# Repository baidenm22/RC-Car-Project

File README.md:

# RC Car Project
This is the repository for all the files in our RC Car Project at BYU in Fall 2026

## The Idea
The goal of this project is to build an RC Car and controller using a microcontroller. We have the following learning goals:
  - Make a PCB
  - Apply our learning of circuits
  - Practice documentation
  - practice using git
  - Create a controller that can be used in all future projects
  - Create friendship
  - Will Simmons needs to lock in
  - Will are you even seeing this
  - Will we need you to do the math

## What is needed

| Car Componets | Controller Components |
|:----------:|:-------------:|
| Arduino Nano | Arduino ESP32 Nano |
| nRF24l01 | nRf24l01 |
| 2 3-6v Motor | L2C OLED |
| Angle Servo | Joystick |
| H-Bridge (L293D) | 4 Buttons

### How we are currently connecting our project to the microcontroller

#### Controller
| Pin | Componet | 
|:----:|:----:|
|VIN|5v Regulator|
|GND	|GND|
|3.3V|nRF24l01 VCC|
|D13	|nRF24l01 SCK|
|D12	|nRF24l01 MISO|
|D11|	nRF24l01 MOSI|
|D10|	Button 1|
|D9|	Button 2|
|D8|	nRF24l01 CSN|
|D7|	nRF24l01 CE|
|D6| Joystick button SW|
|D3|	Button 3|
|D2|	Button 4|
|A1|	Joystick VRY|
|A2|	Joystick VRX|
|A4| L2C OLED SDA|
|A5| L2C OLED SCL|

#### Car
| Pin | Componet | 
|:----:|:----:|
|VIN|	5v Regulator|
|GND|	GND|
|3.3V|	nRF24l01 VCC|
|D13|	nRF24l01 SCK|
|D12|	nRF24l01 MISO|
|D11|	nRF24l01 MOSI|
|D10|	Right Motor INPUT 1|
|D9|	Right Motor INPUT 2|
|D8|	nRF24l01 CSN|
|D7|	nRF24l01 CE|
|D6|	Servo Instructions|
|D5|	Right Motor PWM Speed|
|D4|	IR Sensor INPUT|
|D3|	Left Motor PWM Speed|
|D2|	Left Motor INPUT 3|
|D1|	Left Motor INPUT 4|

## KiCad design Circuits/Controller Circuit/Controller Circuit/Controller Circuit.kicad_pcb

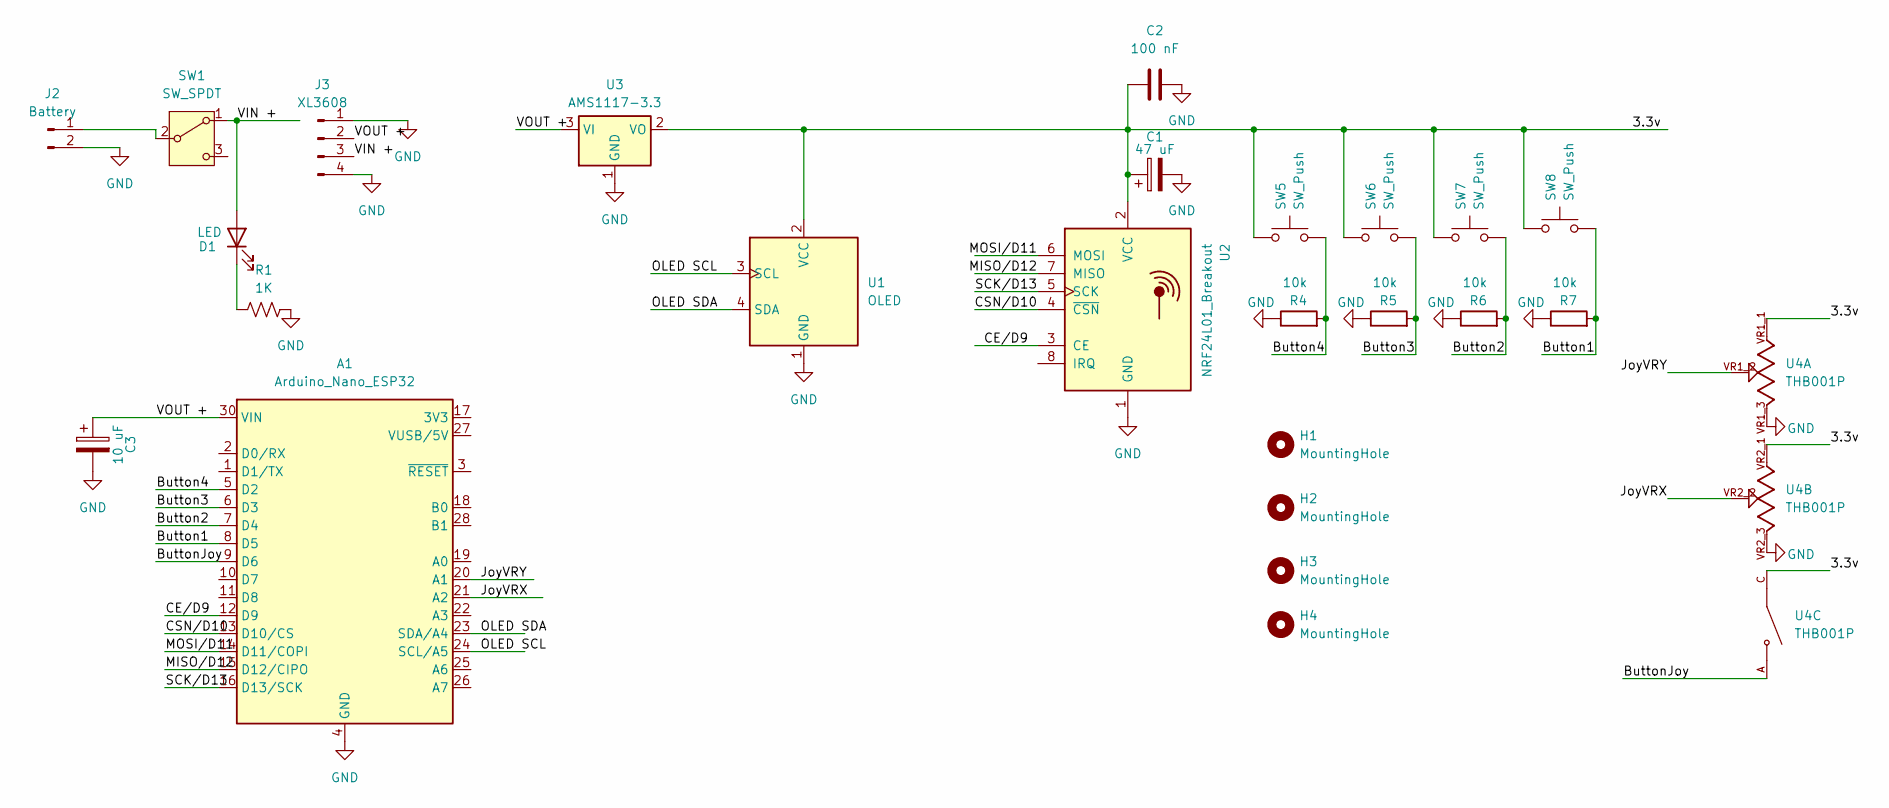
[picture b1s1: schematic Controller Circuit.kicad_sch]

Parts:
A1: Arduino_Nano_ESP32; Arduino_Nano
C1: 47 uF; CP_Radial_D8.0mm_P3.50mm
C2: 100 nF; C_Disc_D4.7mm_W2.5mm_P5.00mm
C3: 10 uF; CP_Radial_D5.0mm_P2.50mm
D1: LED; LED_Oval_W5.2mm_H3.8mm
H1, H2, H3, H4: MountingHole; MountingHole_3.2mm_M3
J2: Battery; SolderWire-0.1sqmm_1x02_P3.6mm_D0.4mm_OD1mm
J3: XL3608; 5V Booster
R1: 1K; R_Axial_DIN0204_L3.6mm_D1.6mm_P5.08mm_Horizontal
R4, R5, R6, R7: 10k; R_Axial_DIN0204_L3.6mm_D1.6mm_P5.08mm_Horizontal
SW1: SW_SPDT; SW_Slide_10mm
SW5, SW6, SW7, SW8: SW_Push; SW_PUSH_6mm
U1: OLED; ER_OLEDM0.91_1x-I2C
U2: NRF24L01_Breakout; nRF24L01_Breakout
U3: AMS1117-3.3; PinSocket_1x03_P2.54mm_Horizontal
U4: THB001P; CNK_THB001P; MPN THB001P

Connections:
/3.3v: C1.1, C2.2, SW5.1, SW6.1, SW7.1, SW8.1, U1.2 (VCC), U2.2 (VCC), U3.2 (VO), U4.C, U4.D, U4.VR1_1, U4.VR2_1
/Button1: A1.8 (D5), R7.2, SW8.2
/Button2: A1.7 (D4), R6.2, SW7.2
/Button3: A1.6 (D3), R5.2, SW6.2
/Button4: A1.5 (D2), R4.2, SW5.2
/ButtonJoy: A1.9 (D6), U4.A, U4.B
/CE/D9: A1.12 (D9), U2.3 (CE)
/CSN/D10: A1.13 (D10/CS), U2.4 (~CSN)
/JoyVRX: A1.21 (A2), U4.VR2_2
/JoyVRY: A1.20 (A1), U4.VR1_2
/MISO/D12: A1.15 (D12/CIPO), U2.7 (MISO)
/MOSI/D11: A1.14 (D11/COPI), U2.6 (MOSI)
/OLED SCL: A1.24 (SCL/A5), U1.3 (SCL)
/OLED SDA: A1.23 (SDA/A4), U1.4 (SDA)
/SCK/D13: A1.16 (D13/SCK), U2.5 (SCK)
/VIN +: D1.2 (A), J3.3, SW1.1 (A)
/VOUT +: A1.30 (VIN), C3.1, J3.2, U3.3 (VI)
GND: A1.4 (GND), A1.29 (GND), C1.2, C2.1, C3.2, J2.2, J3.1, J3.4, R1.2, R4.1, R5.1, R6.1, R7.1, U1.1 (GND), U2.1 (GND), U3.1 (GND), U4.VR1_3, U4.VR2_3
unnamed: D1.1 (K), R1.1
unnamed: J2.1, SW1.2 (B)

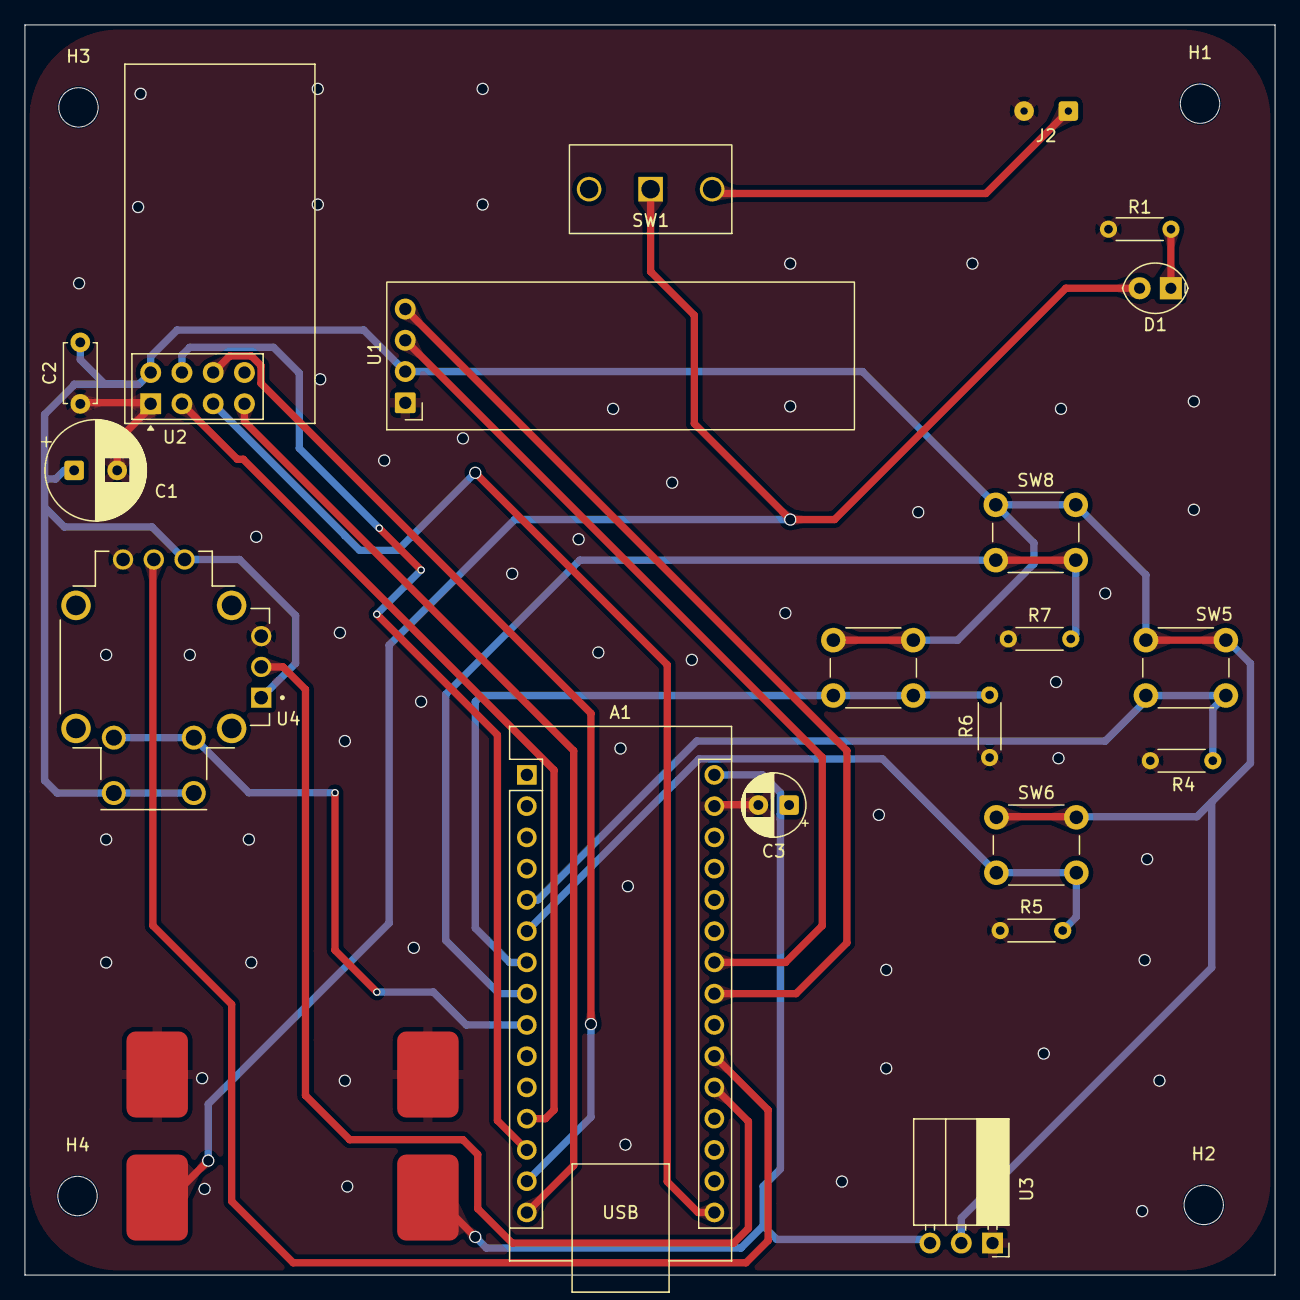
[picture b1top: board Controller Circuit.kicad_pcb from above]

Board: 2 copper layers, 101.6 x 101.6 mm, 25 parts (0 on the bottom side), 20 nets.

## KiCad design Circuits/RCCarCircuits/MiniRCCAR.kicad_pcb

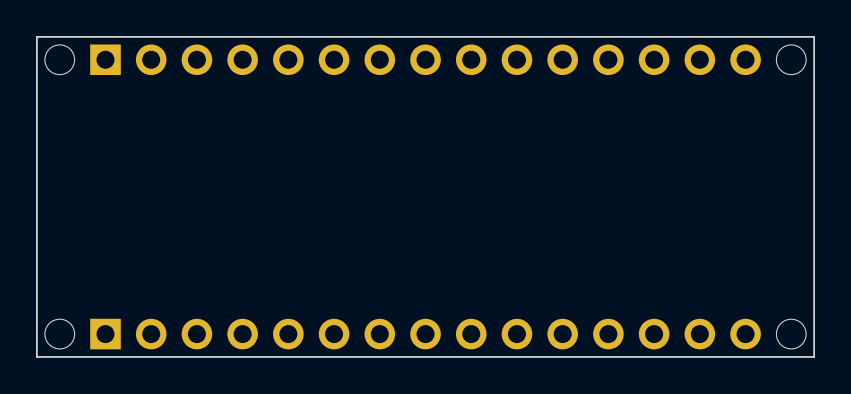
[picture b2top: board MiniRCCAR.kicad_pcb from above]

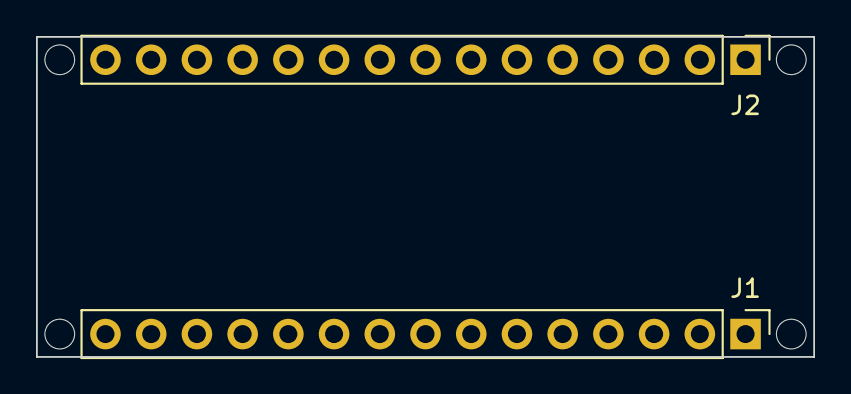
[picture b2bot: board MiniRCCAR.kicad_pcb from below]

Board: 2 copper layers, 43.2 x 17.8 mm, 6 parts (2 on the bottom side), 2 nets, no tracks yet.

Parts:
J1: Analog; PinHeader_1x15_P2.54mm_Vertical
J2: Digital; PinHeader_1x15_P2.54mm_Vertical
MH1, MH2, MH3, MH4: MountingHole_65mil

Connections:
/~RESET: J1.13, J2.13
GND: J1.14, J2.12

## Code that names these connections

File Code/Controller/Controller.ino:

//This is the radio library
#include <RF24.h>
#include <RF24_config.h>
#include <nRF24L01.h>
#define CE_PIN 7
#define CSN_PIN 10
RF24 radio(CE_PIN, CSN_PIN);
const byte address[6][6] = {"00001","00002","00003","00004","00005","00006"};
uint8_t selectedAddress = 0;

//This is the OLED library
#include <Wire.h>
#include <Adafruit_GFX.h>
#include <Adafruit_SSD1306.h>
#define SCREEN_WIDTH 128 // OLED display width, in pixels
#define SCREEN_HEIGHT 32 // OLED display height, in pixels
#define OLED_RESET -1 // Reset pin # (or -1 if sharing Arduino reset pin)
Adafruit_SSD1306 display(SCREEN_WIDTH, SCREEN_HEIGHT, &Wire, OLED_RESET);


uint8_t button1 = 8;
uint8_t button2 = 9;
uint8_t button3 = 3;
uint8_t button4 = 2;
uint8_t joyStickButton = 6;
uint8_t joyStickX = 2;
uint8_t joyStickY = 1;

char buffer[32];

/*
PUESDO CODE:

Initial Communication:
  1. Connect with the car
  2. Select Channel (Show Channel and All)
  3. Send Channel
  4. Switch Channel
  5. Confirm reconnection





*/
struct packet {
  uint16_t joystickX; //2 bytes
  uint16_t joystickY; //2 bytes
  uint8_t joystickButton; //1 byte
  uint8_t button1; //1 byte
  uint8_t button2; //1 byte
  uint8_t button3; //1 byte
  uint8_t button4; // 1 byte
  //1 byte padding
  //total: 10 bytes, so 22 bytes avliable to send
} data;




void setPins() {
  pinMode(button1, INPUT);
  pinMode(button2, INPUT);
  pinMode(button3, INPUT);
  pinMode(button4, INPUT);
  pinMode(joyStickButton, INPUT_PULLUP);
}

void setChannel() {
  bool selectedChannel = false;
  sprintf(buffer, "Current Channel: %d", selectedAddress);
  display.print(buffer);
  display.display();
  while(!selectedChannel){
    if(digitalRead(button1)) {
      delay(500);
      selectedAddress = (selectedAddress + 1) % 6;
      sprintf(buffer, "Current Channel: %d", selectedAddress);
      display.setCursor(0,0);
      display.clearDisplay();
      display.print(buffer);
      display.display();
    }
    if(digitalRead(button2)) {
      delay(500);
      selectedAddress = (selectedAddress + 5) % 6;
      sprintf(buffer, "Current Channel: %d", selectedAddress);
      display.setCursor(0,0);
      display.clearDisplay();
      display.print(buffer);
      display.display();
    }
    if(digitalRead(button3)) {
      delay(500);
      if(radio.write(&selectedAddress, sizeof(selectedAddress))){
        radio.openWritingPipe(address[selectedAddress]);
        selectedChannel = true;
      } else {
        display.setCursor(0,0);
        display.clearDisplay();
        display.print("Failed to connect: Retry");
        display.display();
        delay(2000);
      }
    }
  }
}


void setup() {
  //Set the Pins
  setPins();
  display.begin(SSD1306_SWITCHCAPVCC, 0x3c);
  delay(1000);
  display.setTextColor(WHITE);
  display.clearDisplay();
  display.setTextSize(1);
  display.setCursor(0,0);

  if(!radio.begin())
  {
    display.print("Failed to start Radio");
  }
  delay(1000);
  radio.openWritingPipe(address[selectedAddress]);
  radio.setPALevel(RF24_PA_MIN);
  radio.stopListening();
  setChannel();

}

void loop() {
  // put your main code here, to run repeatedly:
  display.setCursor(0,0);
  sprintf(buffer, "1: %d 2: %d 3: %d 4: %d\n", digitalRead(button1),digitalRead(button2),digitalRead(button3),digitalRead(button4));
  display.println(buffer);
  radio.writeFast(&buffer, sizeof(buffer));
  sprintf(buffer, "X: %d, Y: %d, B: %d\n ", analogRead(joyStickX),analogRead(joyStickY),digitalRead(joyStickButton));
  display.println(buffer);
  display.display();
  delay(250);
  radio.writeFast(&buffer, sizeof(buffer));
  display.clearDisplay();
}
